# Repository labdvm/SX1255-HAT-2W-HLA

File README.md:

# SX1255-HAT-2W-HLA
# 2W High Linearity Amplifier for SX1255 HAT or HS.
# This is PA for SX1255 board like "sxceiver".
# Z32IT

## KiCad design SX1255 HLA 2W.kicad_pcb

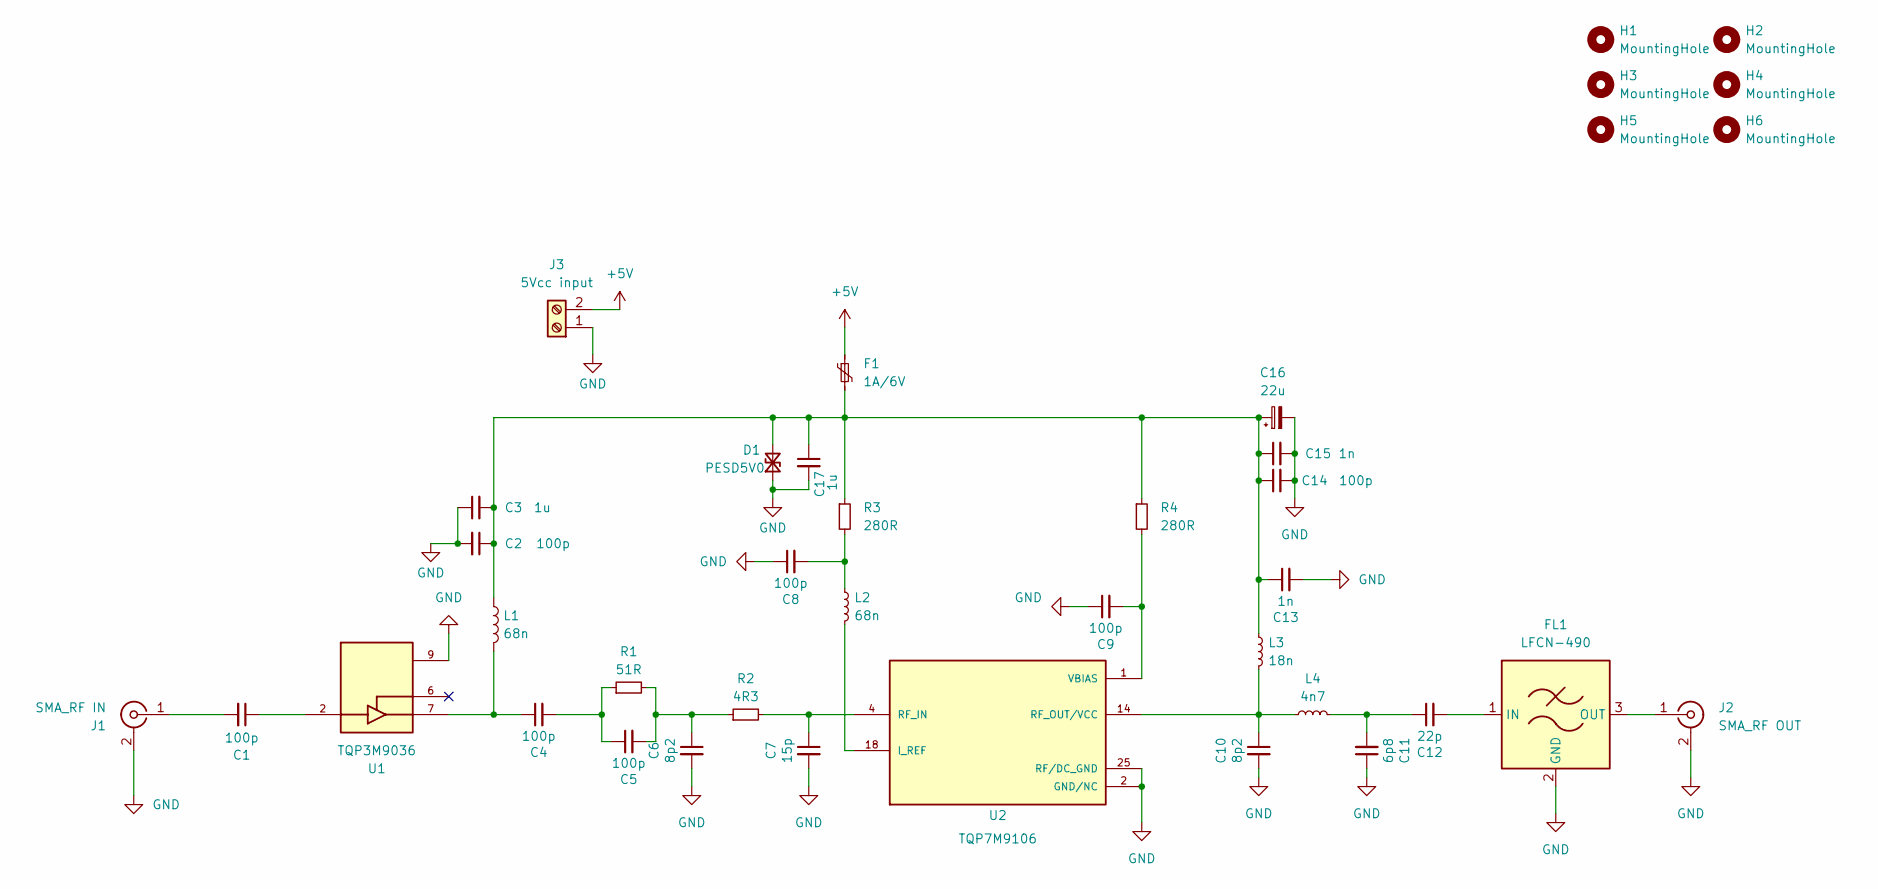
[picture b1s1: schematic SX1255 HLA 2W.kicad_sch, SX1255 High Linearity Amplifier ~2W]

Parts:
C1, C2, C4, C5, C8, C9, C14: 100p; C_0603_1608Metric
C3, C17: 1u; C_0603_1608Metric
C6, C10: 8p2; C_0603_1608Metric
C7: 15p; C_0603_1608Metric
C11: 6p8; C_0603_1608Metric
C12: 22p; C_0603_1608Metric
C13, C15: 1n; C_0603_1608Metric
C16: 22u; CP_EIA-6032-28_Kemet-C
D1: PESD5V0; D_SOD-323
F1: 1A/6V; Fuse_1206_3216Metric
FL1: LFCN-490; Filter_Mini-Circuits_FV1206
H1, H2, H3, H4, H5, H6: MountingHole; MountingHole_2.2mm_M2_DIN965_Pad
J1: SMA_RF IN; SMA_Edge_6.3mm
J2: SMA_RF OUT; SMA_Edge_6.3mm
J3: 5Vcc input; TerminalBlock_bornier-2_P5.08mm
L1: 68n; L_0805_2012Metric
L2: 68n; L_0603_1608Metric
L3: 18n; L_1008_2520Metric
L4: 4n7; L_0603_1608Metric
R1: 51R; R_0603_1608Metric
R2: 4R3; R_0603_1608Metric
R3, R4: 280R; R_0603_1608Metric
U1: TQP3M9036; SON50P200X200X95-9N; PARTREV N/A
U2: TQP7M9106; QFN50P400X400X90-25N; PARTREV Rev.D

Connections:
+5V: F1.1, J3.2
GND: C2.2, C3.1, C6.2, C7.2, C8.1, C9.1, C10.2, C11.1, C13.2, C14.2, C15.2, C16.2, C17.2, D1.1 (A1), FL1.2 (GND), FL1.4 (GND), H1.1, H2.1, H3.1, H4.1, H5.1, H6.1, J1.2 (Ext), J2.2 (Ext), J3.1, U1.1, U1.3, U1.4, U1.5, U1.8, U1.9, U1.V1, U1.V2, U1.V3, U2.2 (GND/NC), U2.3 (GND/NC), U2.6 (GND/NC), U2.7 (GND/NC), U2.8 (GND/NC), U2.9 (GND/NC), U2.10 (GND/NC), U2.11 (GND/NC), U2.12 (GND/NC), U2.13 (GND/NC), U2.17 (GND/NC), U2.19 (GND/NC), U2.20 (GND/NC), U2.21 (GND/NC), U2.22 (GND/NC), U2.23 (GND/NC), U2.24 (GND/NC), U2.25 (RF/DC_GND), U2.26 (RF/DC_GND)
unnamed: C1.1, U1.2
unnamed: C4.1, L1.2, U1.7
unnamed: C4.2, C5.1, R1.1
unnamed: C5.2, C6.1, R1.2, R2.1
unnamed: C7.1, R2.2, U2.4 (RF_IN), U2.5 (RF_IN)
unnamed: C8.2, L2.1, R3.2
unnamed: C10.1, L3.2, L4.1, U2.14 (RF_OUT/VCC), U2.15 (RF_OUT/VCC), U2.16 (RF_OUT/VCC)
unnamed: C11.2, C12.1, L4.2
unnamed: C2.1, C3.2, C13.1, C14.1, C15.1, C16.1, C17.1, D1.2 (A2), F1.2, L1.1, L3.1, R3.1, R4.1
unnamed: C12.2, FL1.1 (IN)
unnamed: FL1.3 (OUT), J2.1 (In)
unnamed: C1.2, J1.1 (In)
unnamed: L2.2, U2.18 (I_REF)
unnamed: C9.2, R4.2, U2.1 (VBIAS)

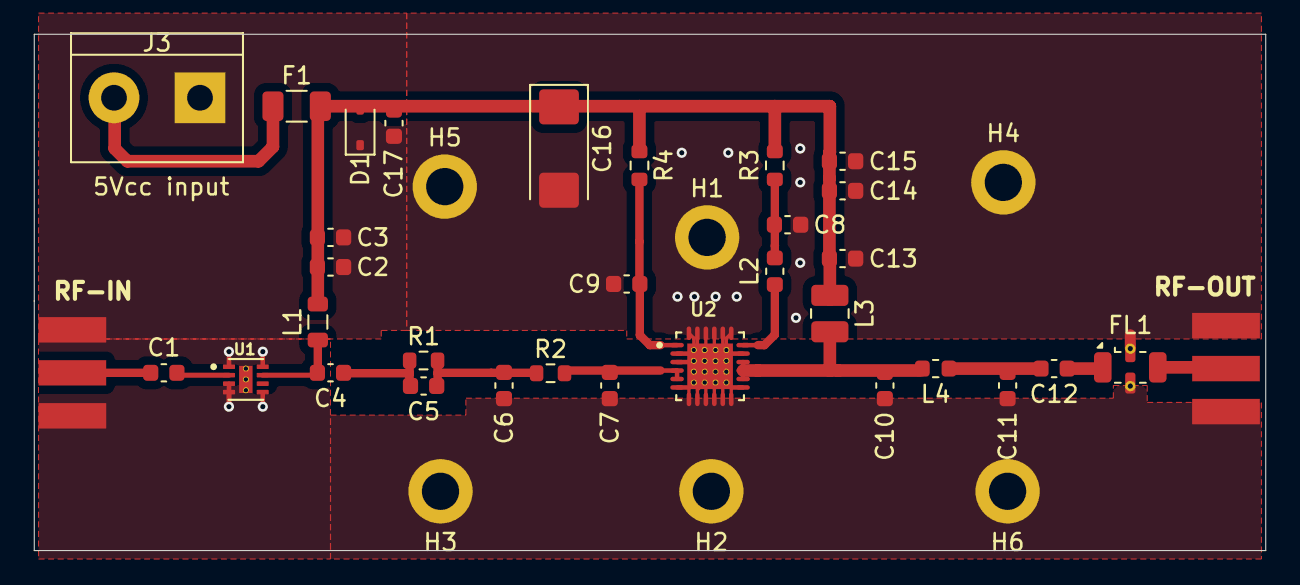
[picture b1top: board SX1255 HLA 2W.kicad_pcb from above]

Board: 2 copper layers, 72.8 x 30.5 mm, 39 parts (0 on the bottom side), 16 nets.
